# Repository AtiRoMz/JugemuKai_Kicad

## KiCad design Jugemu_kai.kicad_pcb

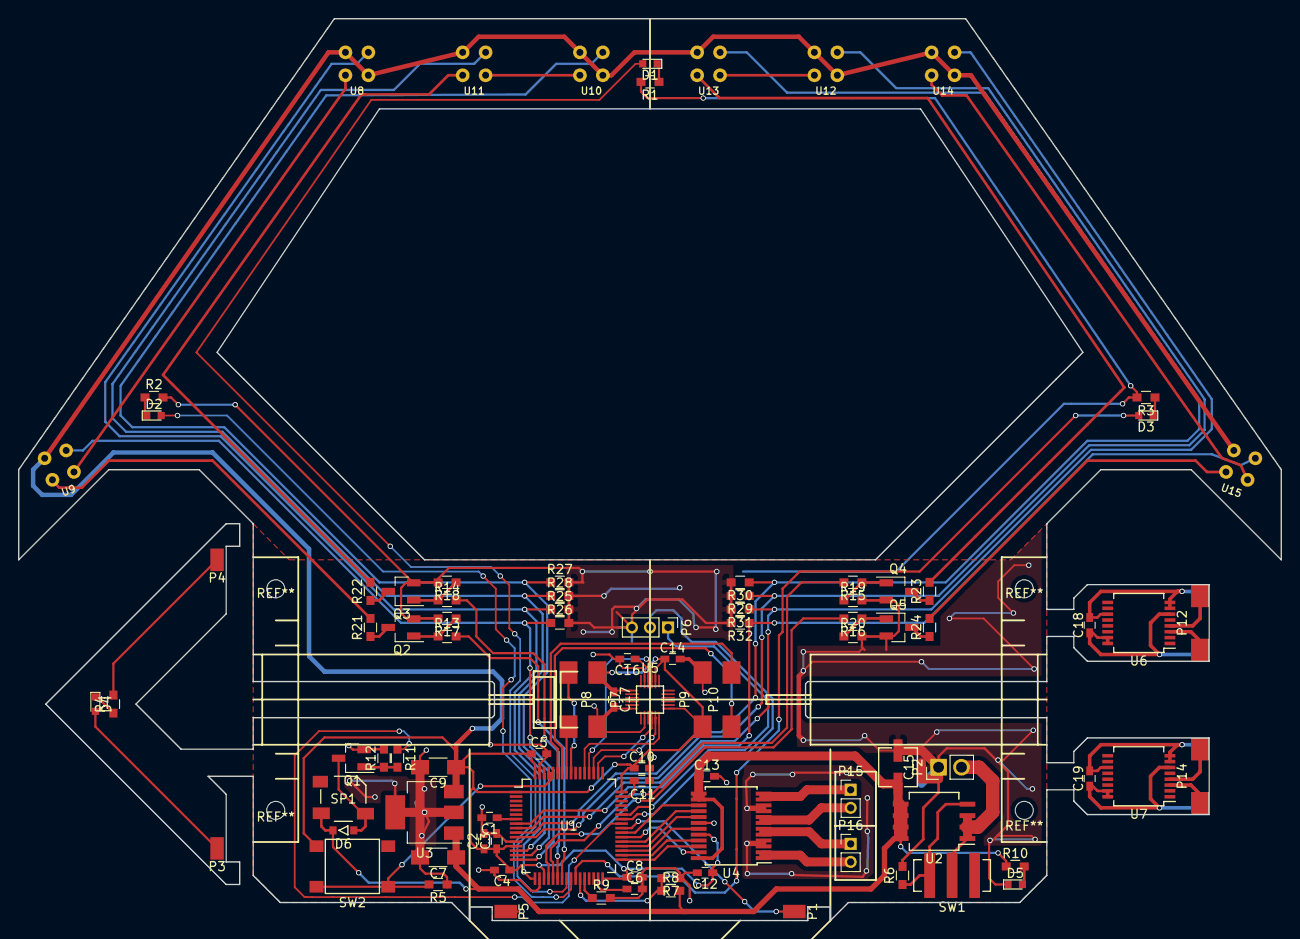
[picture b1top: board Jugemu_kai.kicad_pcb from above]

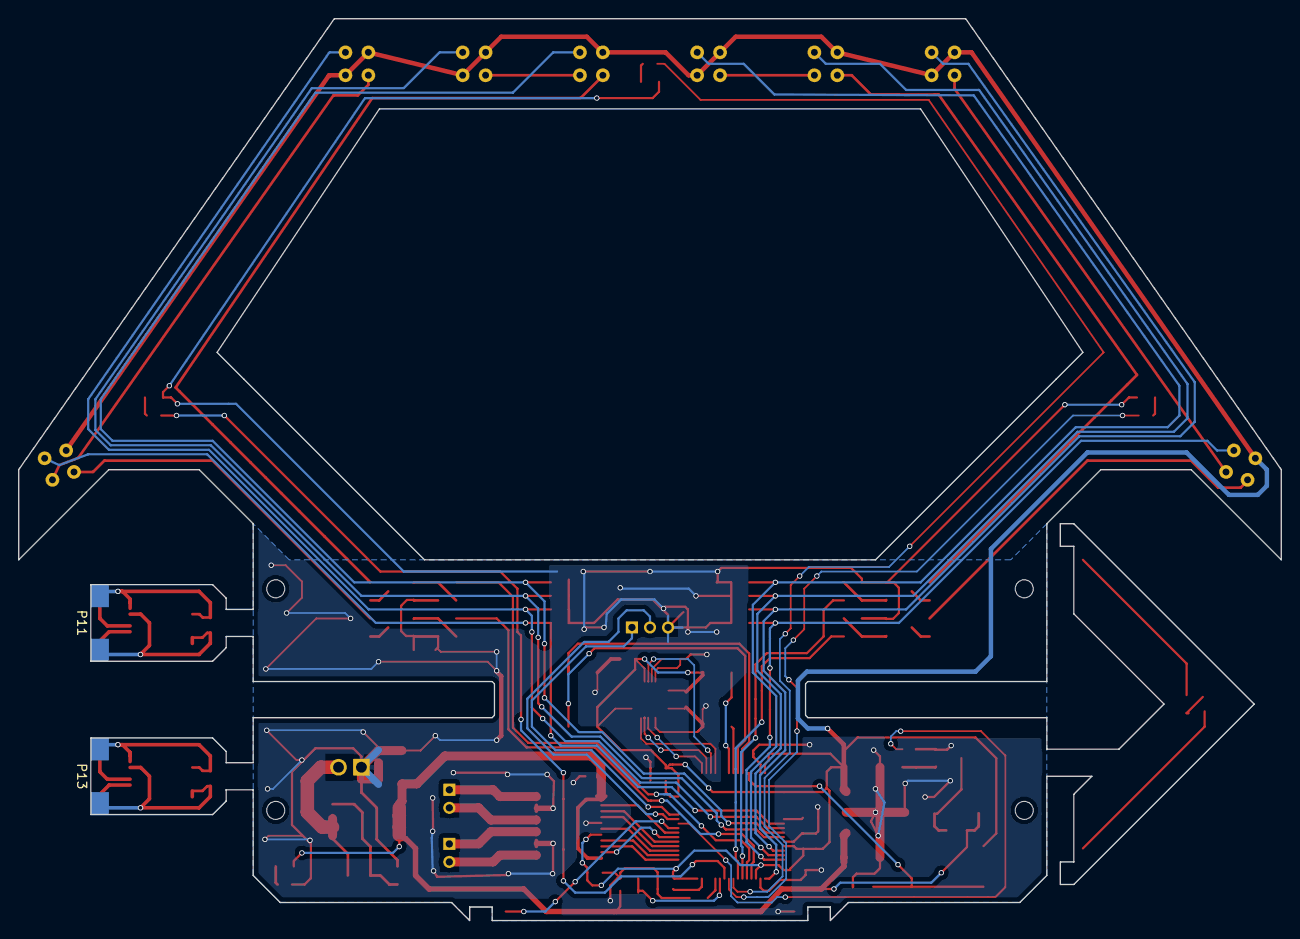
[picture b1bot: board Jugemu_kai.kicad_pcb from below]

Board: 2 copper layers, 140.0 x 100.0 mm, 96 parts (2 on the bottom side), 83 nets.

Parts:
C1, C3, C4, C5, C8, C10, C12, C13, C16, C17, C18, C19: 0.1u; C_0603_HandSoldering
C2: 1u; C_0603_HandSoldering
C6, C11: 2.2u; C_0603_HandSoldering
C7, C9: 10u; C_1206_HandSoldering
C14: 0.01u; C_0603_HandSoldering
C15: 10u; AlumiC
D1, D2, D3, D4: LED; LED_0603
D5: Led_Small; LED_0603
D6: D_Schottky_Small; CUS520
P1, P3, P4, P5: CONN_01X01; CON_TAIL
P2: CONN_01X02; Pin_Header_Straight_1x02_Pitch2.54mm
P6: CONN_01X03; Pin_Header_Straight_1x03_Pitch2.00mm
P7, P8, P9, P10, P11, P12, P13, P14: CONN_01X02; ENC_CON
P15, P16: CONN_01X02; Pin_Header_Straight_1x02_Pitch2.00mm
Q1, Q2, Q3, Q4, Q5: IRLML6344; SOT-23_Handsoldering
R1, R2, R3, R4: 200; R_0603_HandSoldering
R5, R7, R8, R9: 10k; R_0603_HandSoldering
R6: 47k; R_0603_HandSoldering
R10, R11, R13, R14, R15, R16: 470; R_0603_HandSoldering
R12, R17, R18, R19, R20: 100k; R_0603_HandSoldering
R21, R22, R23, R24: 15; R_0603_HandSoldering
R25, R26, R27, R28, R29, R30, R31, R32: 1k; R_0603_HandSoldering
SP1: SPEAKER; SMT-0540-S-R
SW1: SWITCH; CL-SB-22A-01
SW2: SW_PUSH; PTS645SM43
U1: STM32F405RGT6; LQFP64
U2: STS7PF30L; SO-8_5.3x6.2mm_Pitch1.27mm
U3: LT1963A; My_SOT-223
U4: TB6612FNG; SSOP-24_5.3x8.2mm_Pitch0.65mm
U5: MPU-9250; MPU9250
U6, U7: AS5145B; SSOP-16_5.3x6.2mm_Pitch0.65mm
U8: PHOTOTRANSISTOR1; LBR127HLD
U9: PHOTOTRANSISTOR2; LBR127HLD
U10: PHOTOTRANSISTOR3; LBR127HLD
U11: PHOTOTRANSISTOR4; LBR127HLD
U12: PHOTOTRANSISTOR5; LBR127HLD
U13: PHOTOTRANSISTOR6; LBR127HLD
U14: PHOTOTRANSISTOR7; LBR127HLD
U15: PHOTOTRANSISTOR8; LBR127HLD

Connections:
+3V3: C2.1, C3.1, C4.1, C5.1, C8.1, C9.1, C10.1, C12.1, C14.1, C17.1, P7.2, P9.2, SW2.1, U1.1, U1.13, U1.19, U1.32, U1.48, U1.64, U3.3, U4.20, U5.1, U5.8, U5.13, U8.1, U8.4, U9.4, U10.1, U10.4, U11.4, U12.1, U12.4, U13.4, U14.1, U14.4, U15.4
+BATT: C7.1, C13.1, C15.1, D6.1, R8.2, R10.1, SP1.1, U2.5, U2.6, U2.7, U2.8, U3.1, U4.13, U4.14, U4.24
AIN1: U1.34, U4.21
AIN2: U1.33, U4.22
BATT_REF: R7.2, R8.1, U1.27
BIN1: U1.36, U4.17
BIN2: U1.37, U4.16
BUZZER: R11.1, U1.41
CS: U1.50, U5.22
ENC1_A: P8.2, U1.56
ENC1_B: P8.1, U1.57
ENC2_A: P10.2, U1.58
ENC2_B: P10.1, U1.59
GND: C1.2, C2.2, C3.2, C4.2, C5.2, C6.2, C7.2, C8.2, C9.2, C10.2, C11.2, C12.2, C13.2, C14.2, C15.2, C16.2, C17.2, D5.1, P2.1, P5.1, P6.3, P7.1, P9.1, Q1.2, Q2.2, Q3.2, Q4.2, Q5.2, R1.2, R2.2, R3.2, R5.1, R6.2, R7.1, R9.2, R12.2, R17.2, R18.2, R19.2, R20.2, R25.2, R26.2, R27.2, R28.2, R29.2, R30.2, R31.2, R32.2, U1.12, U1.18, U1.63, U3.2, U3.4, U4.3, U4.4, U4.9, U4.10, U4.18, U5.11, U5.18, U5.20
LED12: R13.2, U1.23
LED34: R14.2, U1.22
LED56: R15.2, U1.21
LED78: R16.2, U1.20
MISO: U1.52, U5.9
MOSI: U1.53, U5.24
unnamed: C1.1, U1.7
unnamed: C6.1, U1.31
unnamed: C11.1, U1.47
unnamed: C16.1, U5.10
unnamed: C18.1, P11.2, U6.6, U6.15, U6.16
unnamed: C18.2, P11.1, U6.7, U6.8, U6.11
unnamed: C19.1, P13.2, U7.6, U7.15, U7.16
unnamed: C19.2, P13.1, U7.7, U7.8, U7.11
unnamed: D1.1, R1.1
unnamed: D2.1, R2.1
unnamed: D3.1, R3.1
unnamed: D4.1, R4.1
unnamed: D4.2, P3.1
unnamed: D5.2, R10.2
unnamed: D6.2, Q1.3, SP1.2
unnamed: P2.2, SW1.2, U2.1, U2.2, U2.3
unnamed: P4.1, R4.2
unnamed: P6.1, U1.43
unnamed: P6.2, U1.42
unnamed: P12.1, U6.4
unnamed: P12.2, U6.3
unnamed: P14.1, U7.4
unnamed: P14.2, U7.3
unnamed: P15.1, U4.11, U4.12
unnamed: P15.2, U4.7, U4.8
unnamed: P16.1, U4.5, U4.6
unnamed: P16.2, U4.1, U4.2
unnamed: Q1.1, R11.2, R12.1
unnamed: Q2.1, R13.1, R17.1
unnamed: Q2.3, R21.1
unnamed: Q3.1, R14.1, R18.1
unnamed: Q3.3, R22.1
unnamed: Q4.1, R15.1, R19.1
unnamed: Q4.3, R23.1
unnamed: Q5.1, R16.1, R20.1
unnamed: Q5.3, R24.1
unnamed: R5.2, SW2.2, U1.60, U1.61
unnamed: R6.1, SW1.1, U2.4
unnamed: R9.1, U1.28
unnamed: R21.2, U9.2
unnamed: R22.2, U11.2
unnamed: R23.2, U13.2
unnamed: R24.2, U15.2
unnamed: U8.2, U9.1
unnamed: U10.2, U11.1
unnamed: U12.2, U13.1
unnamed: U14.2, U15.1
PT1: R25.1, U1.17, U8.3
PT2: R26.1, U1.16, U9.3
PT3: R27.1, U1.15, U10.3
PT4: R28.1, U1.14, U11.3
PT5: R29.1, U1.11, U12.3
PT6: R30.1, U1.10, U13.3
PT7: R31.1, U1.9, U14.3
PT8: R32.1, U1.8, U15.3
PWMA: U1.38, U4.23
PWMB: U1.39, U4.15
SCLK: U1.51, U5.23
STBY: U1.35, U4.19
UI_LED1: D1.2, U1.24
UI_LED2: D2.2, U1.25
UI_LED3: D3.2, U1.26
UI_LED4: P1.1, U1.40

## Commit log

2018-05-19 初コミット
